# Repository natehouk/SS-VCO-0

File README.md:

# SS-VCO-0
The original Seattle Synths voltage controlled oscillator.

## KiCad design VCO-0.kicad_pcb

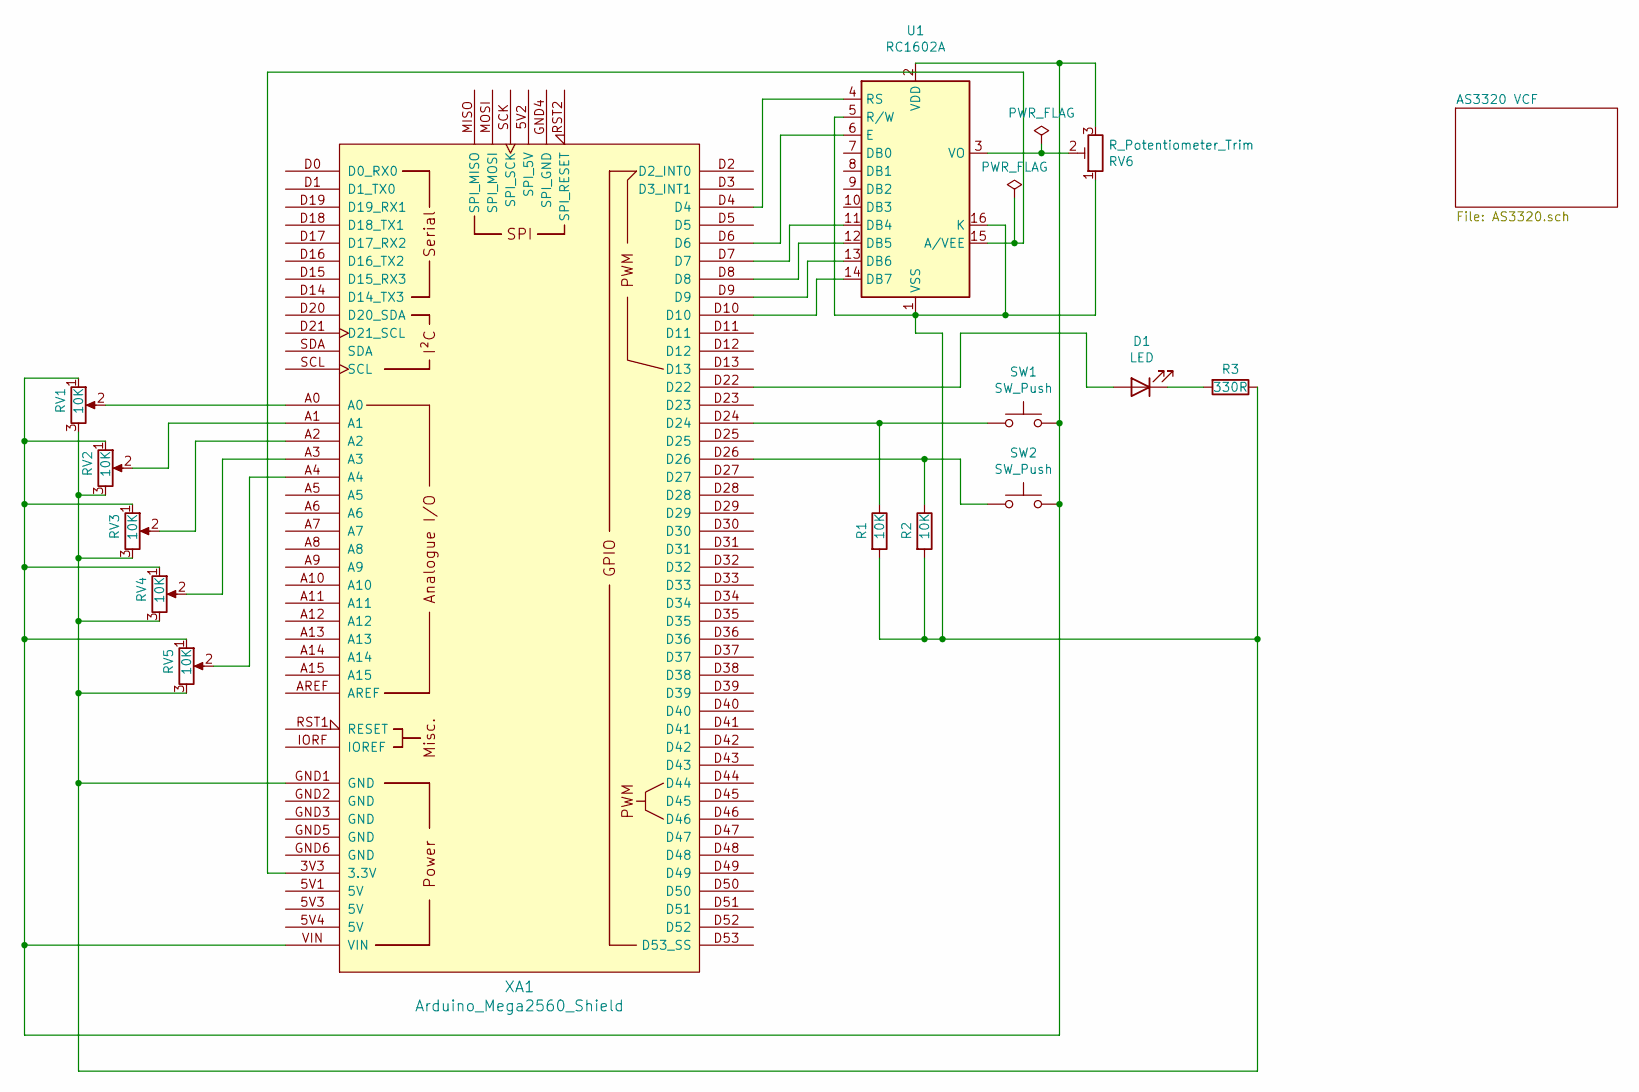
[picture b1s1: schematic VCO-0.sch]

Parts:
D1: LED; LED_D5.0mm
R1, R2: 10K; R_Axial_DIN0207_L6.3mm_D2.5mm_P10.16mm_Horizontal
R3: 330R; R_Axial_DIN0207_L6.3mm_D2.5mm_P10.16mm_Horizontal
RV1, RV2, RV3, RV4, RV5: 10K; Potentiometer_Alps_RK163_Single_Horizontal
RV6: R_Potentiometer_Trim
SW1, SW2: SW_Push; SW_CW_GPTS203211B
U1: RC1602A; WC1602A
XA1: Arduino_Mega2560_Shield

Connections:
unnamed: D1.1 (K), R3.2
unnamed: D1.2 (A), XA1.D22
unnamed: R1.1, SW1.1, XA1.D24
unnamed: R1.2, R2.2, R3.1, RV1.3, RV2.3, RV3.3, RV4.3, RV5.3, RV6.1, U1.1 (VSS), U1.5 (R/W), U1.16 (K), XA1.GND1 (GND)
unnamed: R2.1, SW2.1, XA1.D26
unnamed: RV1.1, RV2.1, RV3.1, RV4.1, RV5.1, RV6.3, SW1.2, SW2.2, U1.2 (VDD), XA1.VIN
unnamed: RV1.2, XA1.A0
unnamed: RV2.2, XA1.A1
unnamed: RV3.2, XA1.A2
unnamed: RV4.2, XA1.A3
unnamed: RV5.2, XA1.A4
unnamed: RV6.2, U1.3 (VO)
unnamed: U1.4 (RS), XA1.D4
unnamed: U1.6 (E), XA1.D6
unnamed: U1.11 (DB4), XA1.D7
unnamed: U1.12 (DB5), XA1.D8
unnamed: U1.13 (DB6), XA1.D9
unnamed: U1.14 (DB7), XA1.D10
unnamed: U1.15 (A/VEE), XA1.3V3 (3.3V)

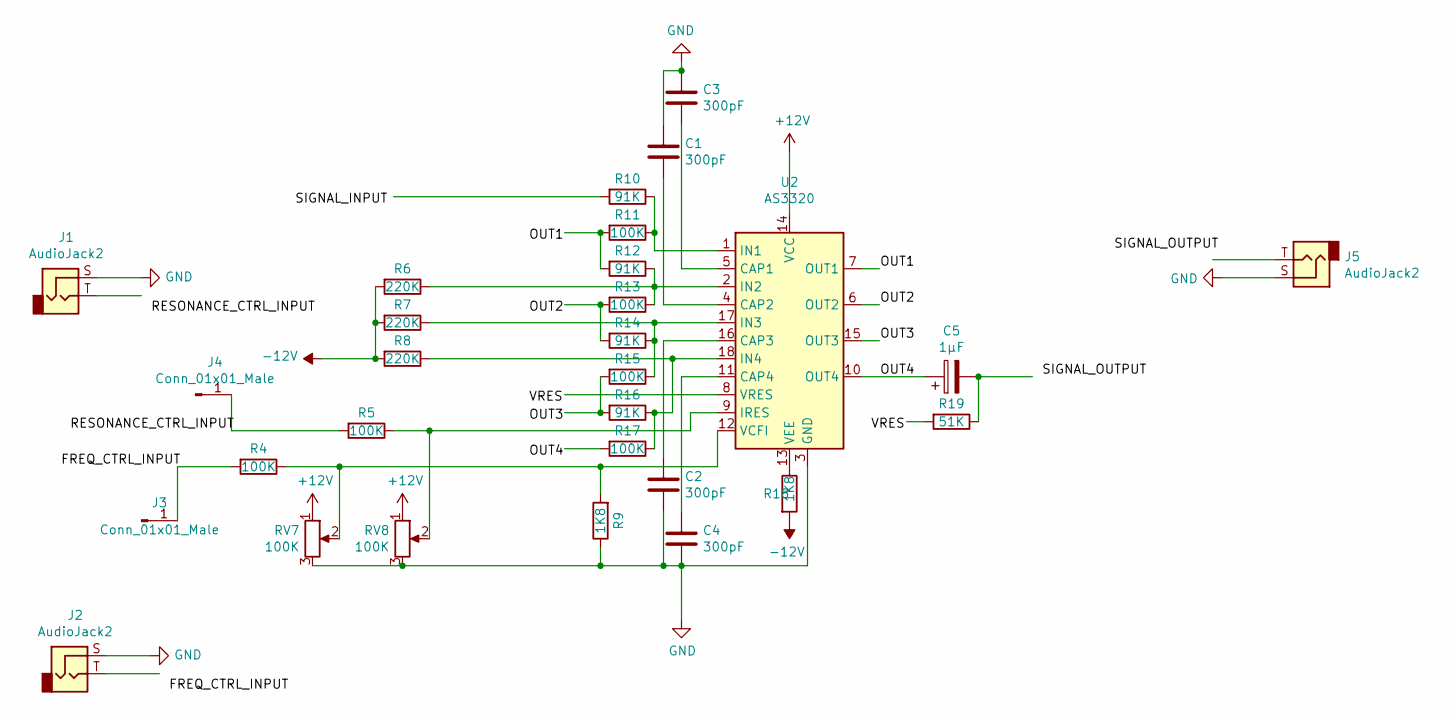
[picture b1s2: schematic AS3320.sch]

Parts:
C1, C2, C3, C4: 300pF; CP_Radial_D5.0mm_P2.50mm
C5: 1µF; CP_Radial_D5.0mm_P2.50mm
J1, J2, J5: AudioJack2; Jack_6.35mm_Neutrik_NJ2FD-V_Vertical
J3, J4: Conn_01x01_Male; Pin_D1.0mm_L10.0mm
R4, R5, R11, R13, R15, R17: 100K; R_Axial_DIN0207_L6.3mm_D2.5mm_P10.16mm_Horizontal
R6, R7, R8: 220K; R_Axial_DIN0207_L6.3mm_D2.5mm_P10.16mm_Horizontal
R9, R18: 1K8; R_Axial_DIN0207_L6.3mm_D2.5mm_P10.16mm_Horizontal
R10, R12, R14, R16: 91K; R_Axial_DIN0207_L6.3mm_D2.5mm_P10.16mm_Horizontal
R19: 51K; R_Axial_DIN0207_L6.3mm_D2.5mm_P10.16mm_Horizontal
RV7, RV8: 100K; Potentiometer_ACP_CA9-V10_Vertical
U2: AS3320; DIP-18_W7.62mm

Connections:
+12V: RV7.1, RV8.1, U2.14 (VCC)
-12V: R6.2, R7.2, R8.2, R18.2
/AS3320 VCF/OUT1: U2.7 (OUT1)
/AS3320 VCF/OUT2: U2.6 (OUT2)
/AS3320 VCF/OUT3: U2.15 (OUT3)
/AS3320 VCF/OUT4: C5.1, U2.10 (OUT4)
GND: C1.1, C2.2, C3.1, C4.2, J1.S, J2.S, J5.S, R9.1, RV7.3, RV8.3, U2.3 (GND)
unnamed: C1.2, U2.4 (CAP2)
unnamed: C2.1, U2.16 (CAP3)
unnamed: C3.2, U2.5 (CAP1)
unnamed: C4.1, U2.11 (CAP4)
unnamed: C5.2, R19.1
unnamed: J3.1, R4.2
unnamed: J4.1, R5.2
unnamed: R4.1, R9.2, RV7.2, U2.12 (VCFI)
unnamed: R5.1, RV8.2, U2.9 (IRES)
unnamed: R10.1, R11.1, U2.1 (IN1)
unnamed: R11.2, R12.2
unnamed: R6.1, R12.1, R13.1, U2.2 (IN2)
unnamed: R13.2, R14.2
unnamed: R7.1, R14.1, R15.1, U2.17 (IN3)
unnamed: R15.2, R16.2
unnamed: R8.1, R16.1, R17.1, U2.18 (IN4)
unnamed: R18.1, U2.13 (VEE)

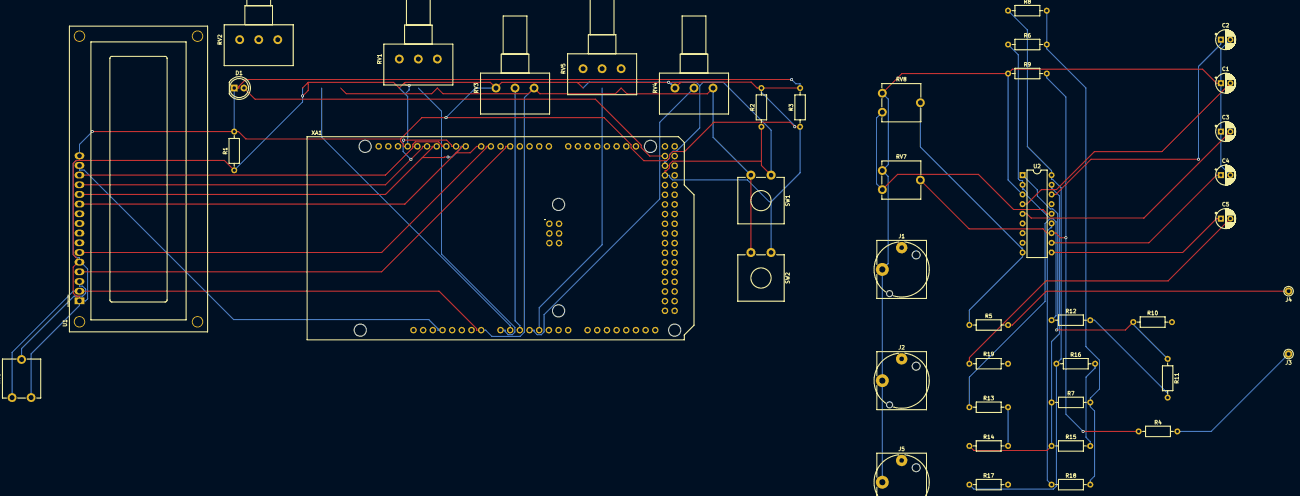
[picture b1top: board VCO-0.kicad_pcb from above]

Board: 2 copper layers, 43 parts (0 on the bottom side), 40 nets.

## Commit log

2020-09-22 Second commit
2020-09-24 Add AS3320 schematic.
2020-09-26 Refactor
